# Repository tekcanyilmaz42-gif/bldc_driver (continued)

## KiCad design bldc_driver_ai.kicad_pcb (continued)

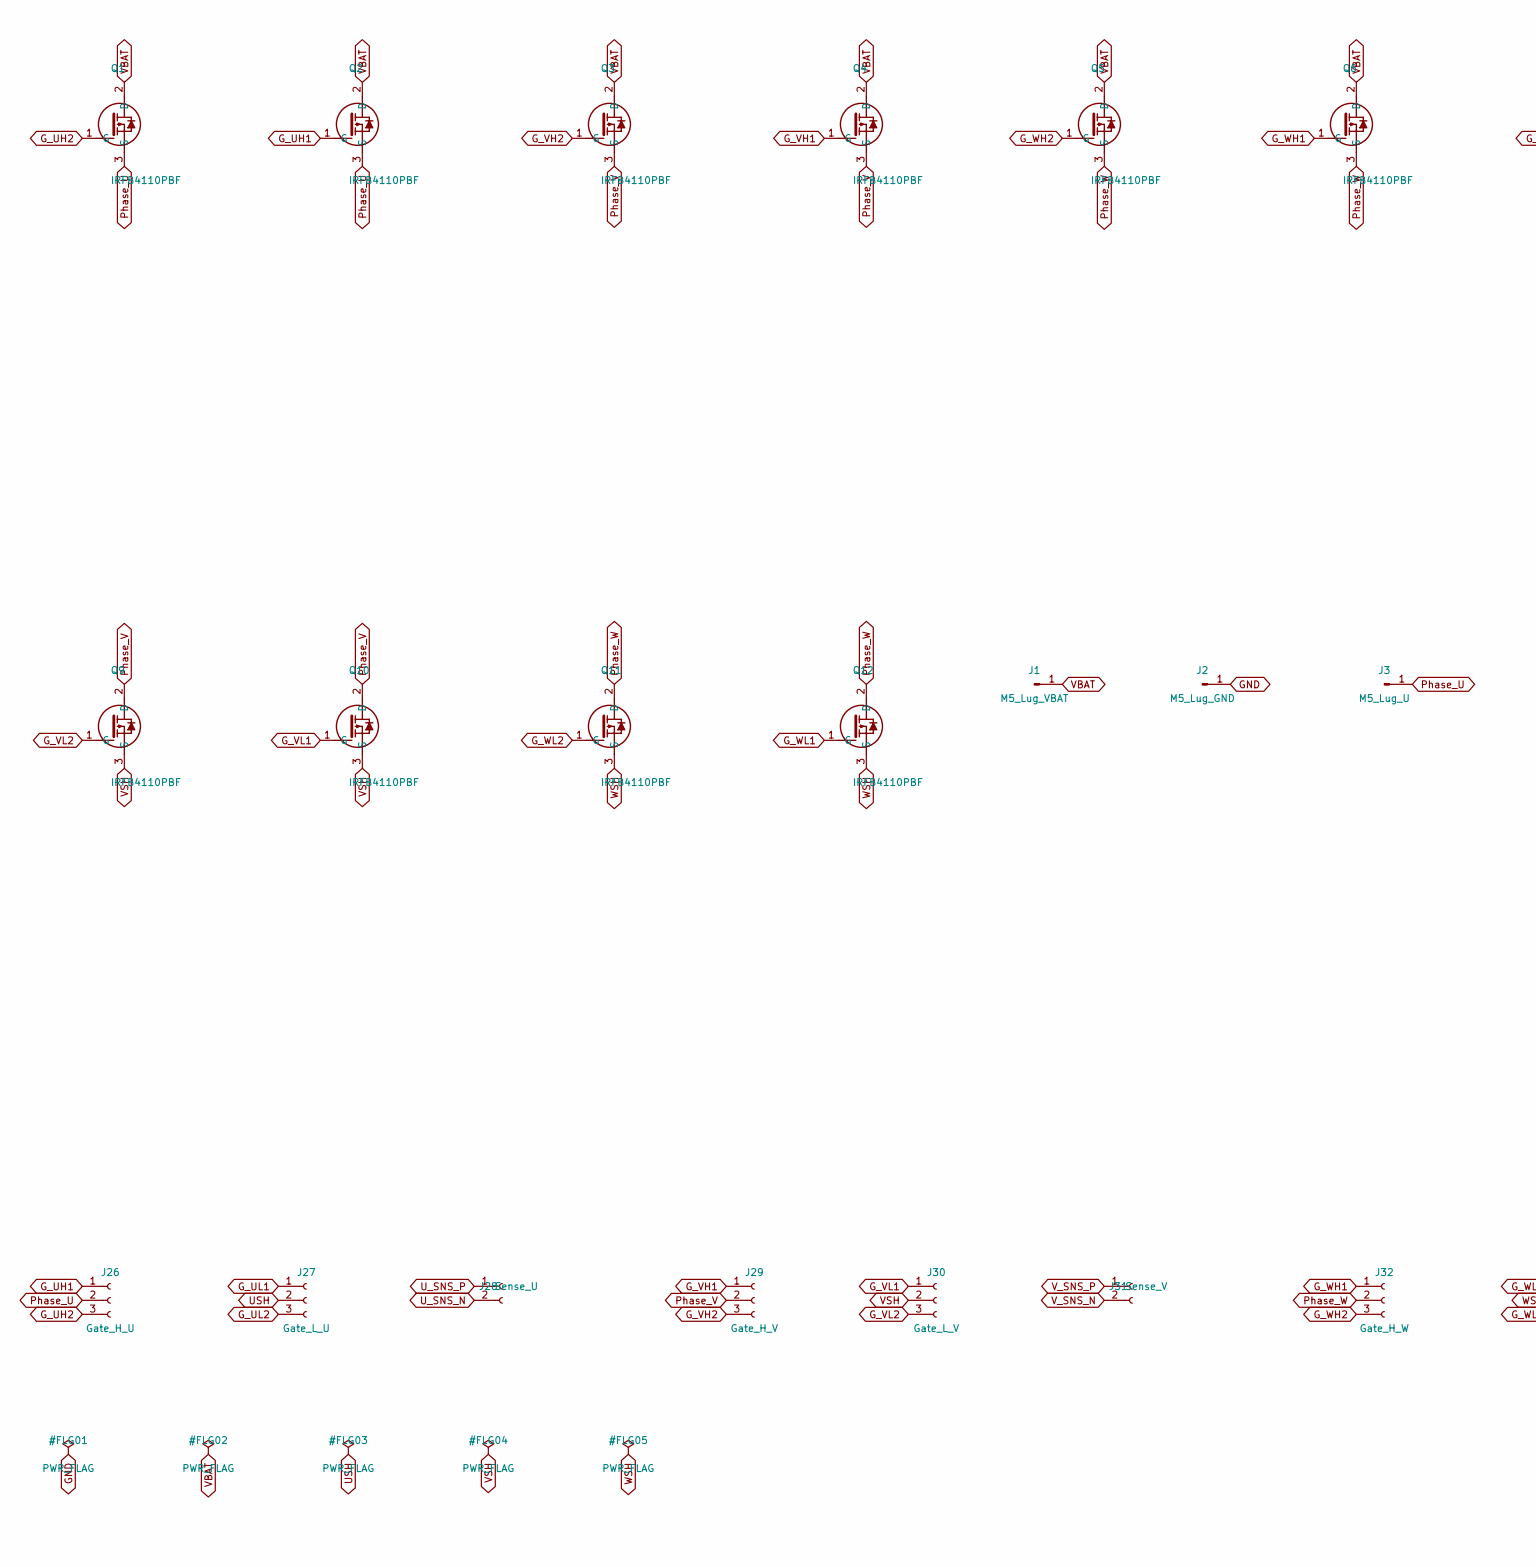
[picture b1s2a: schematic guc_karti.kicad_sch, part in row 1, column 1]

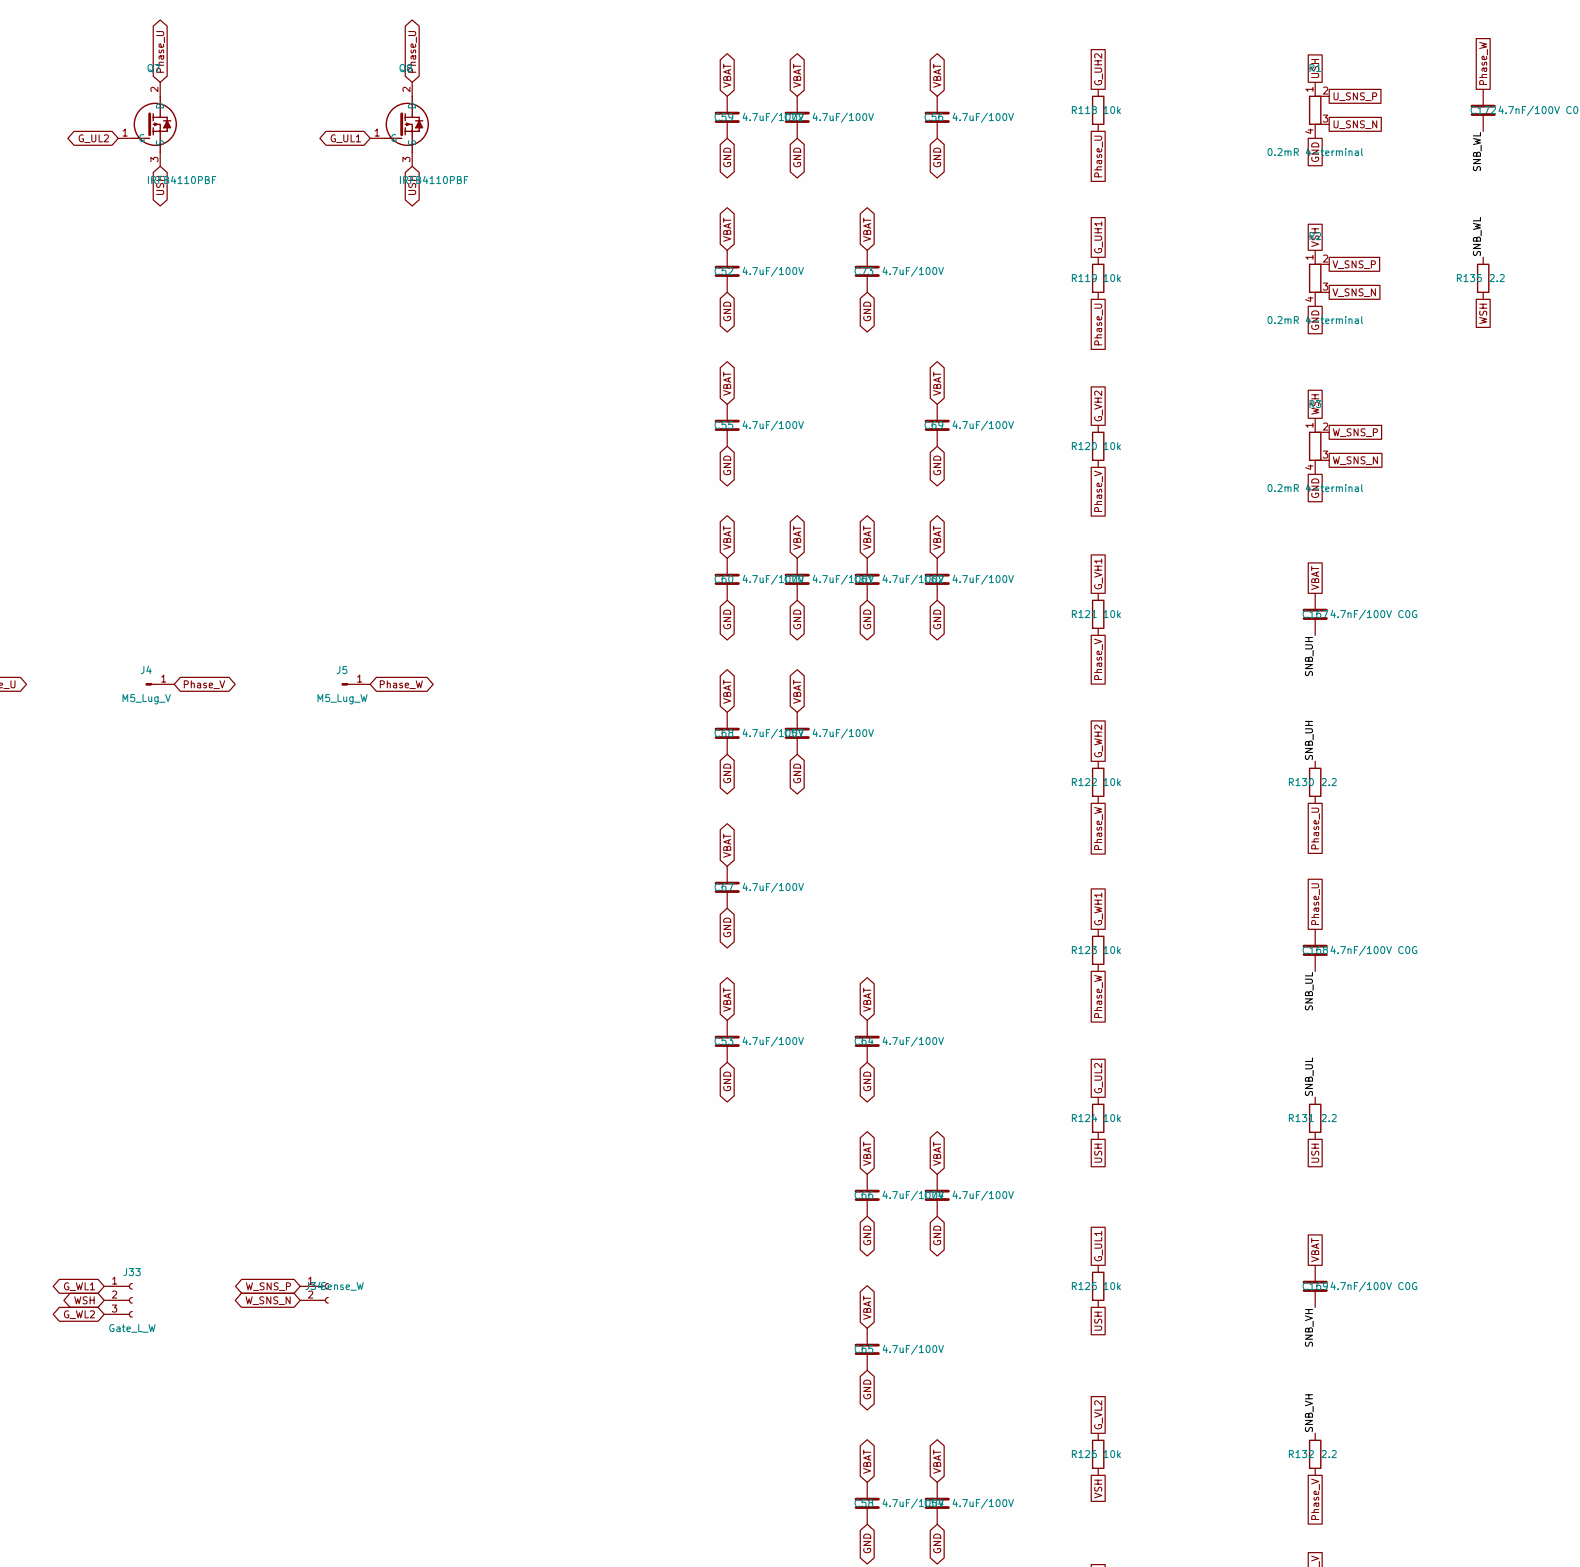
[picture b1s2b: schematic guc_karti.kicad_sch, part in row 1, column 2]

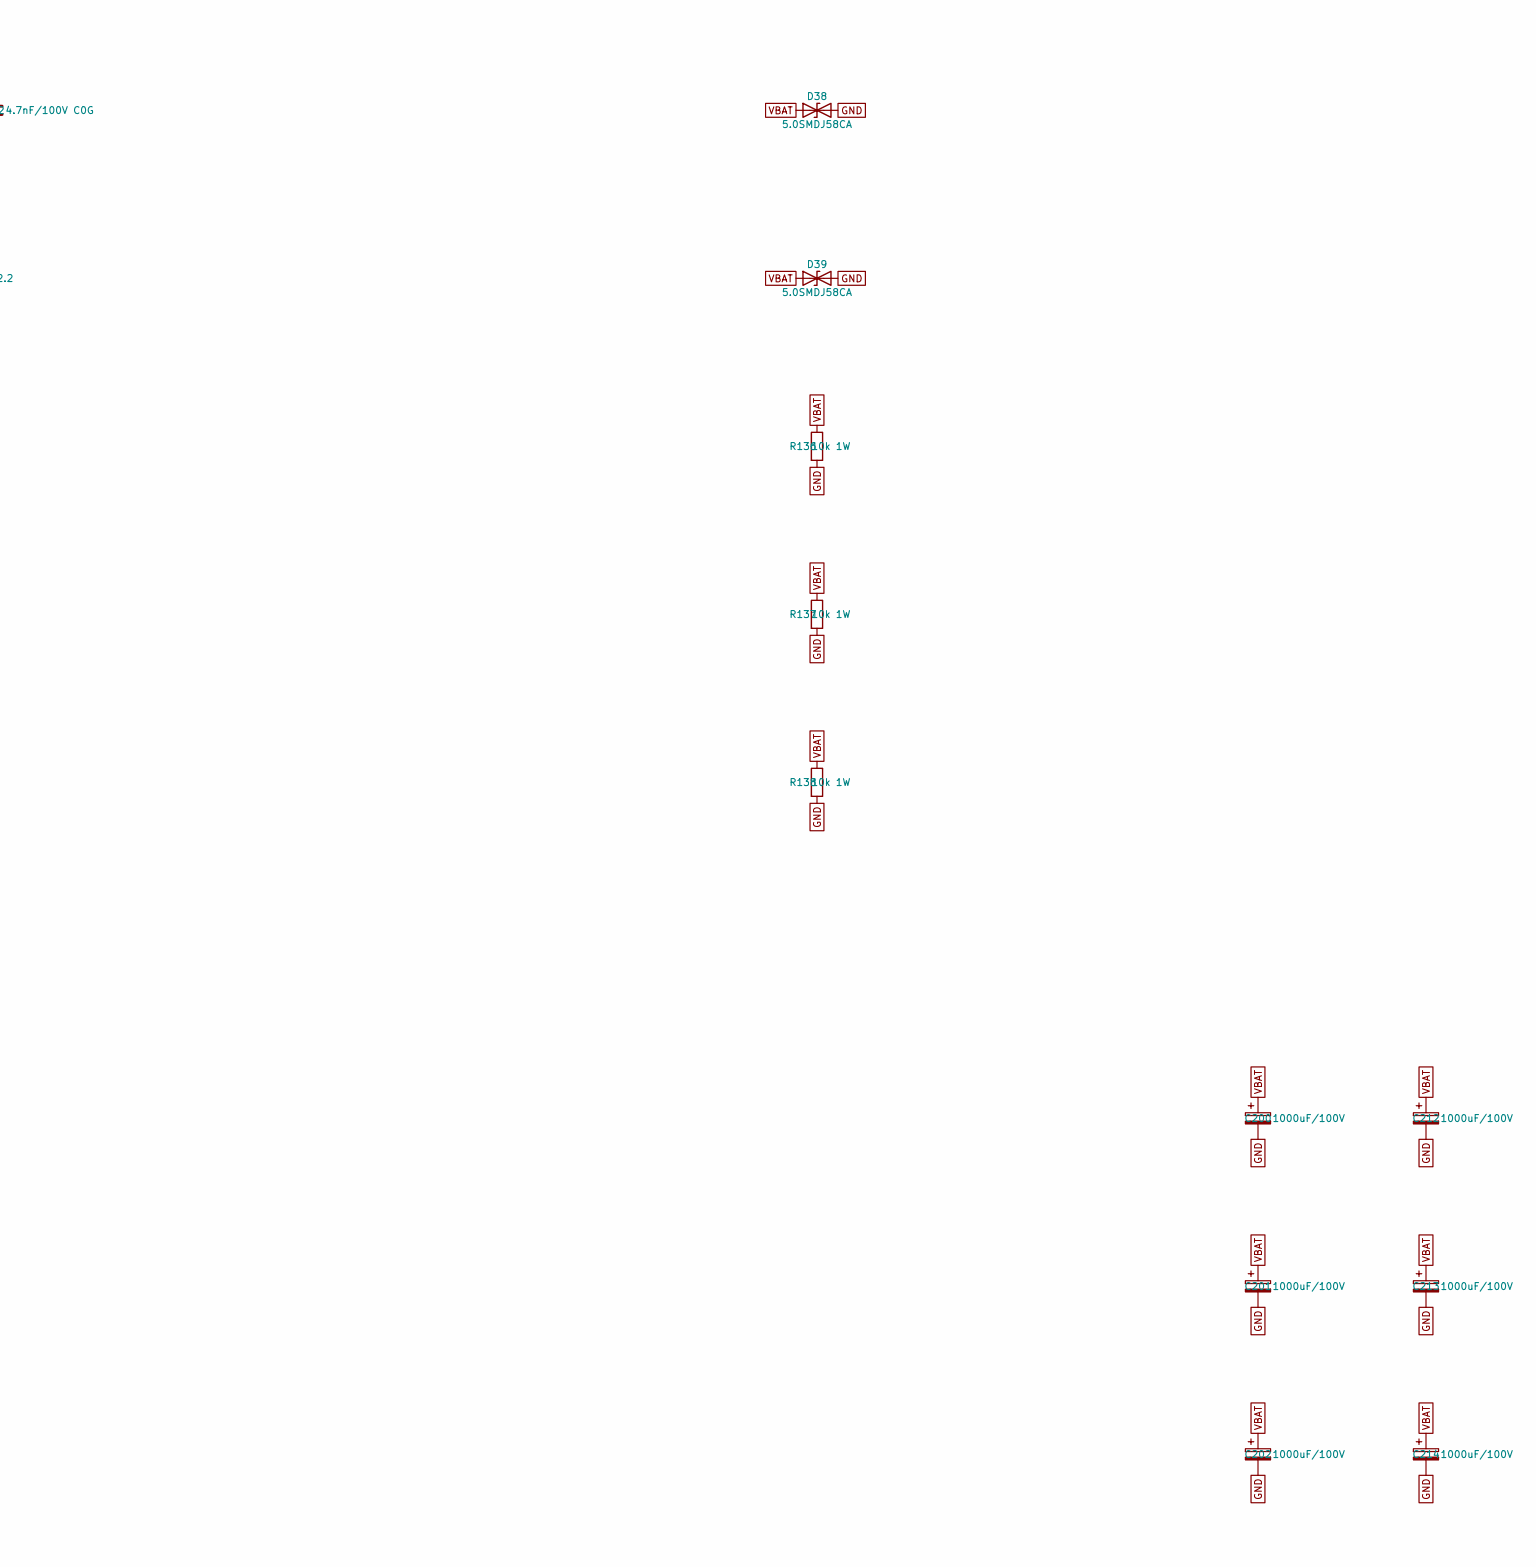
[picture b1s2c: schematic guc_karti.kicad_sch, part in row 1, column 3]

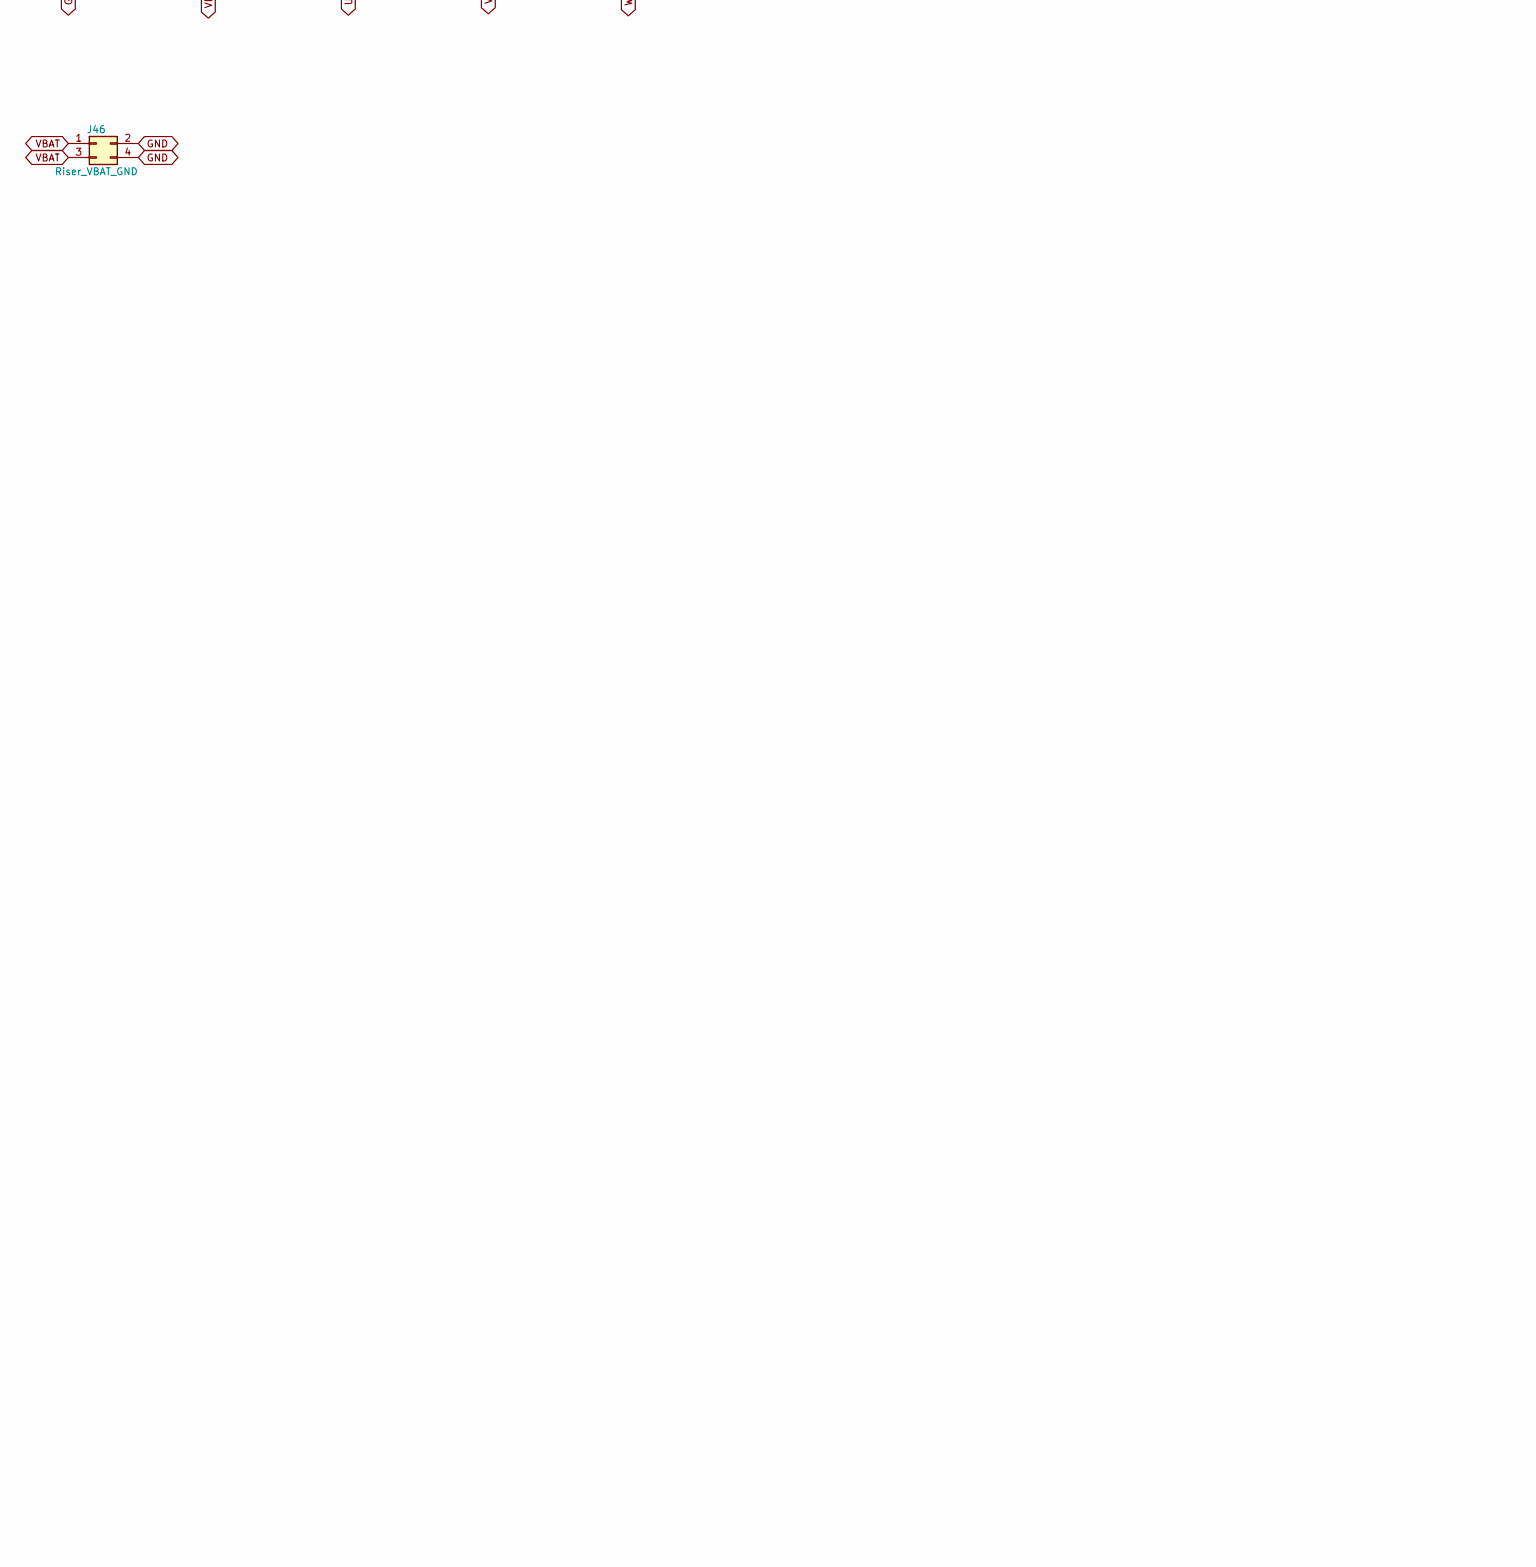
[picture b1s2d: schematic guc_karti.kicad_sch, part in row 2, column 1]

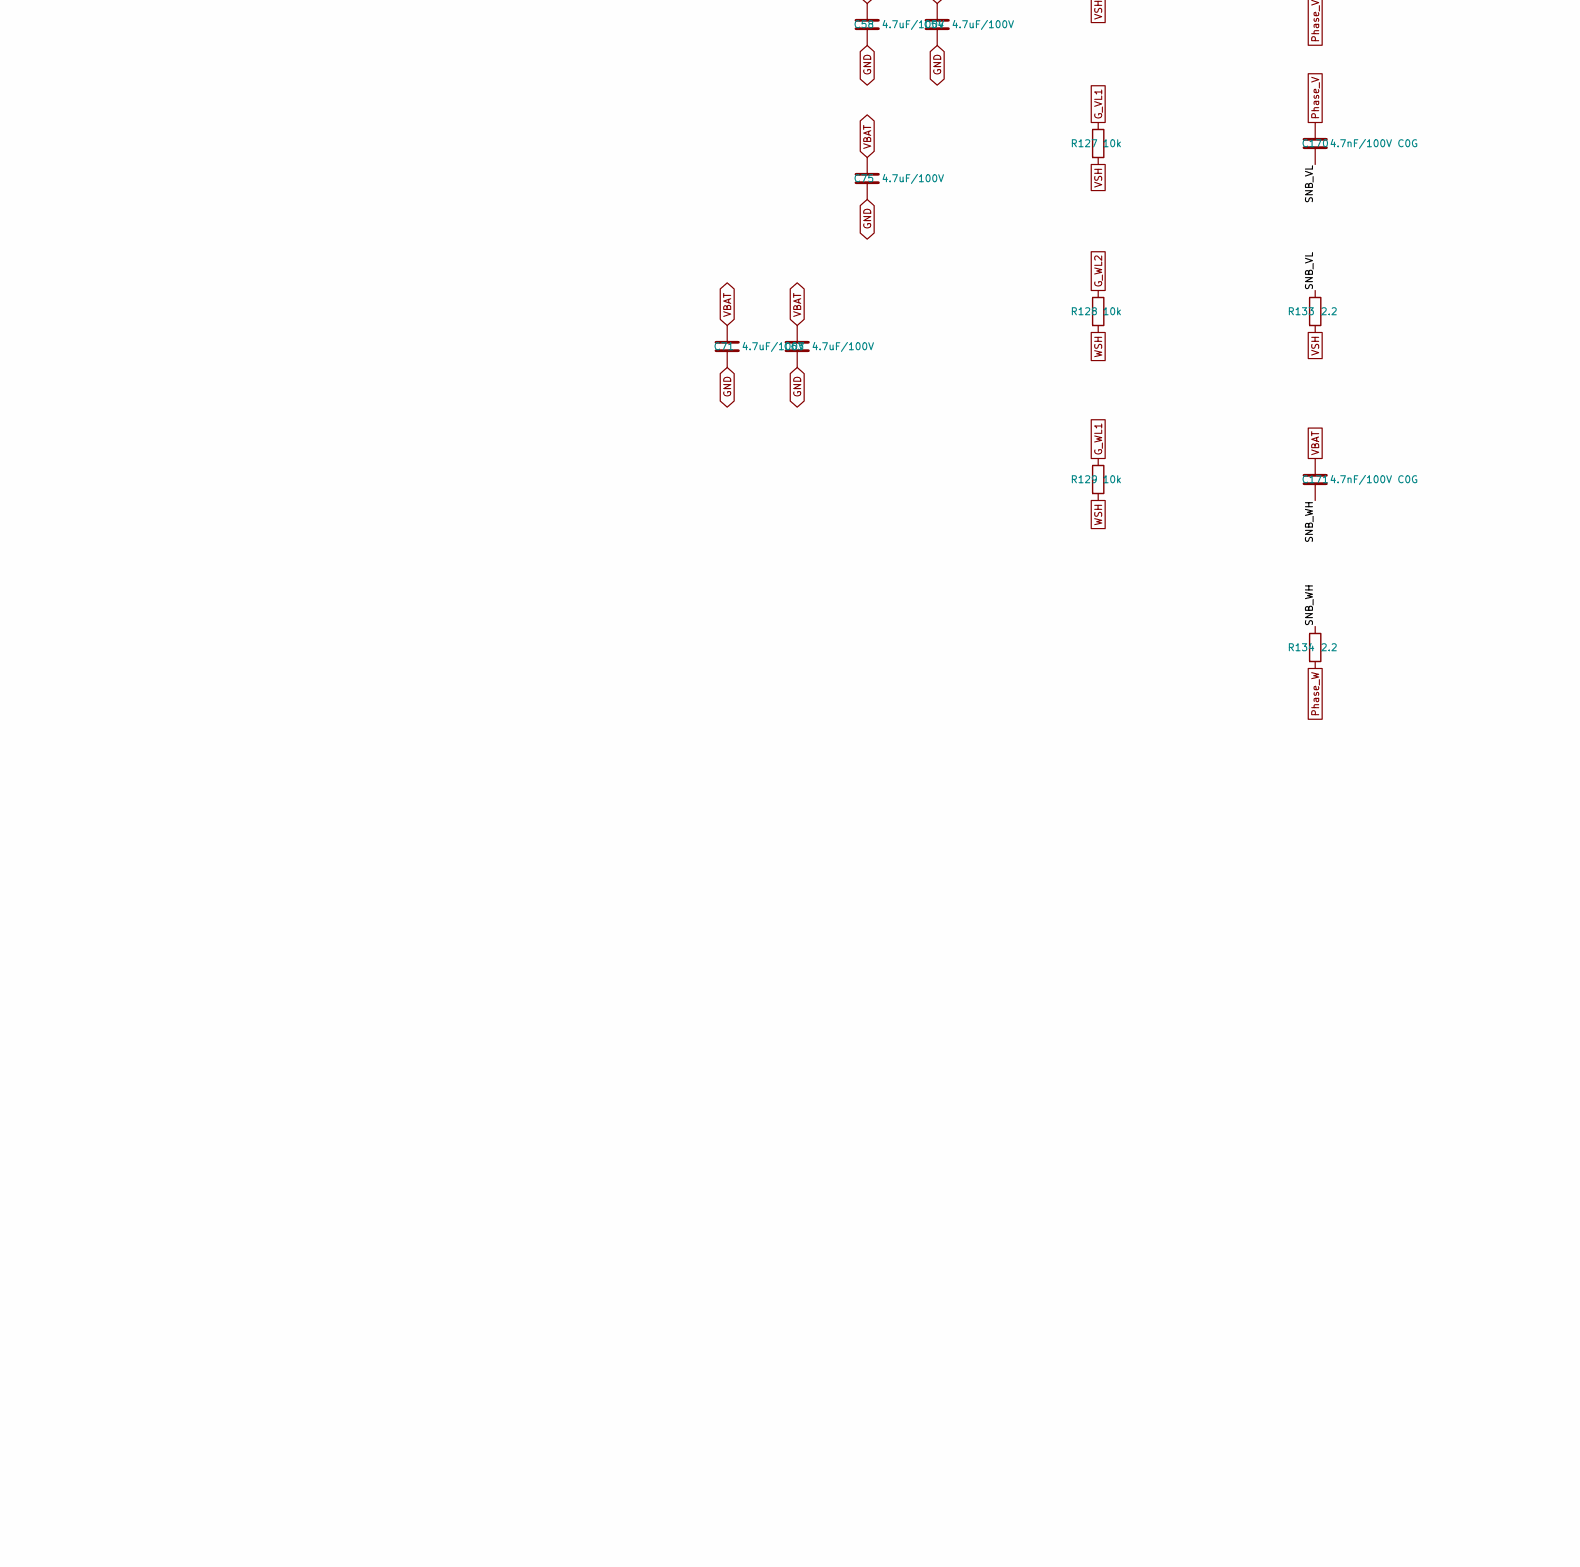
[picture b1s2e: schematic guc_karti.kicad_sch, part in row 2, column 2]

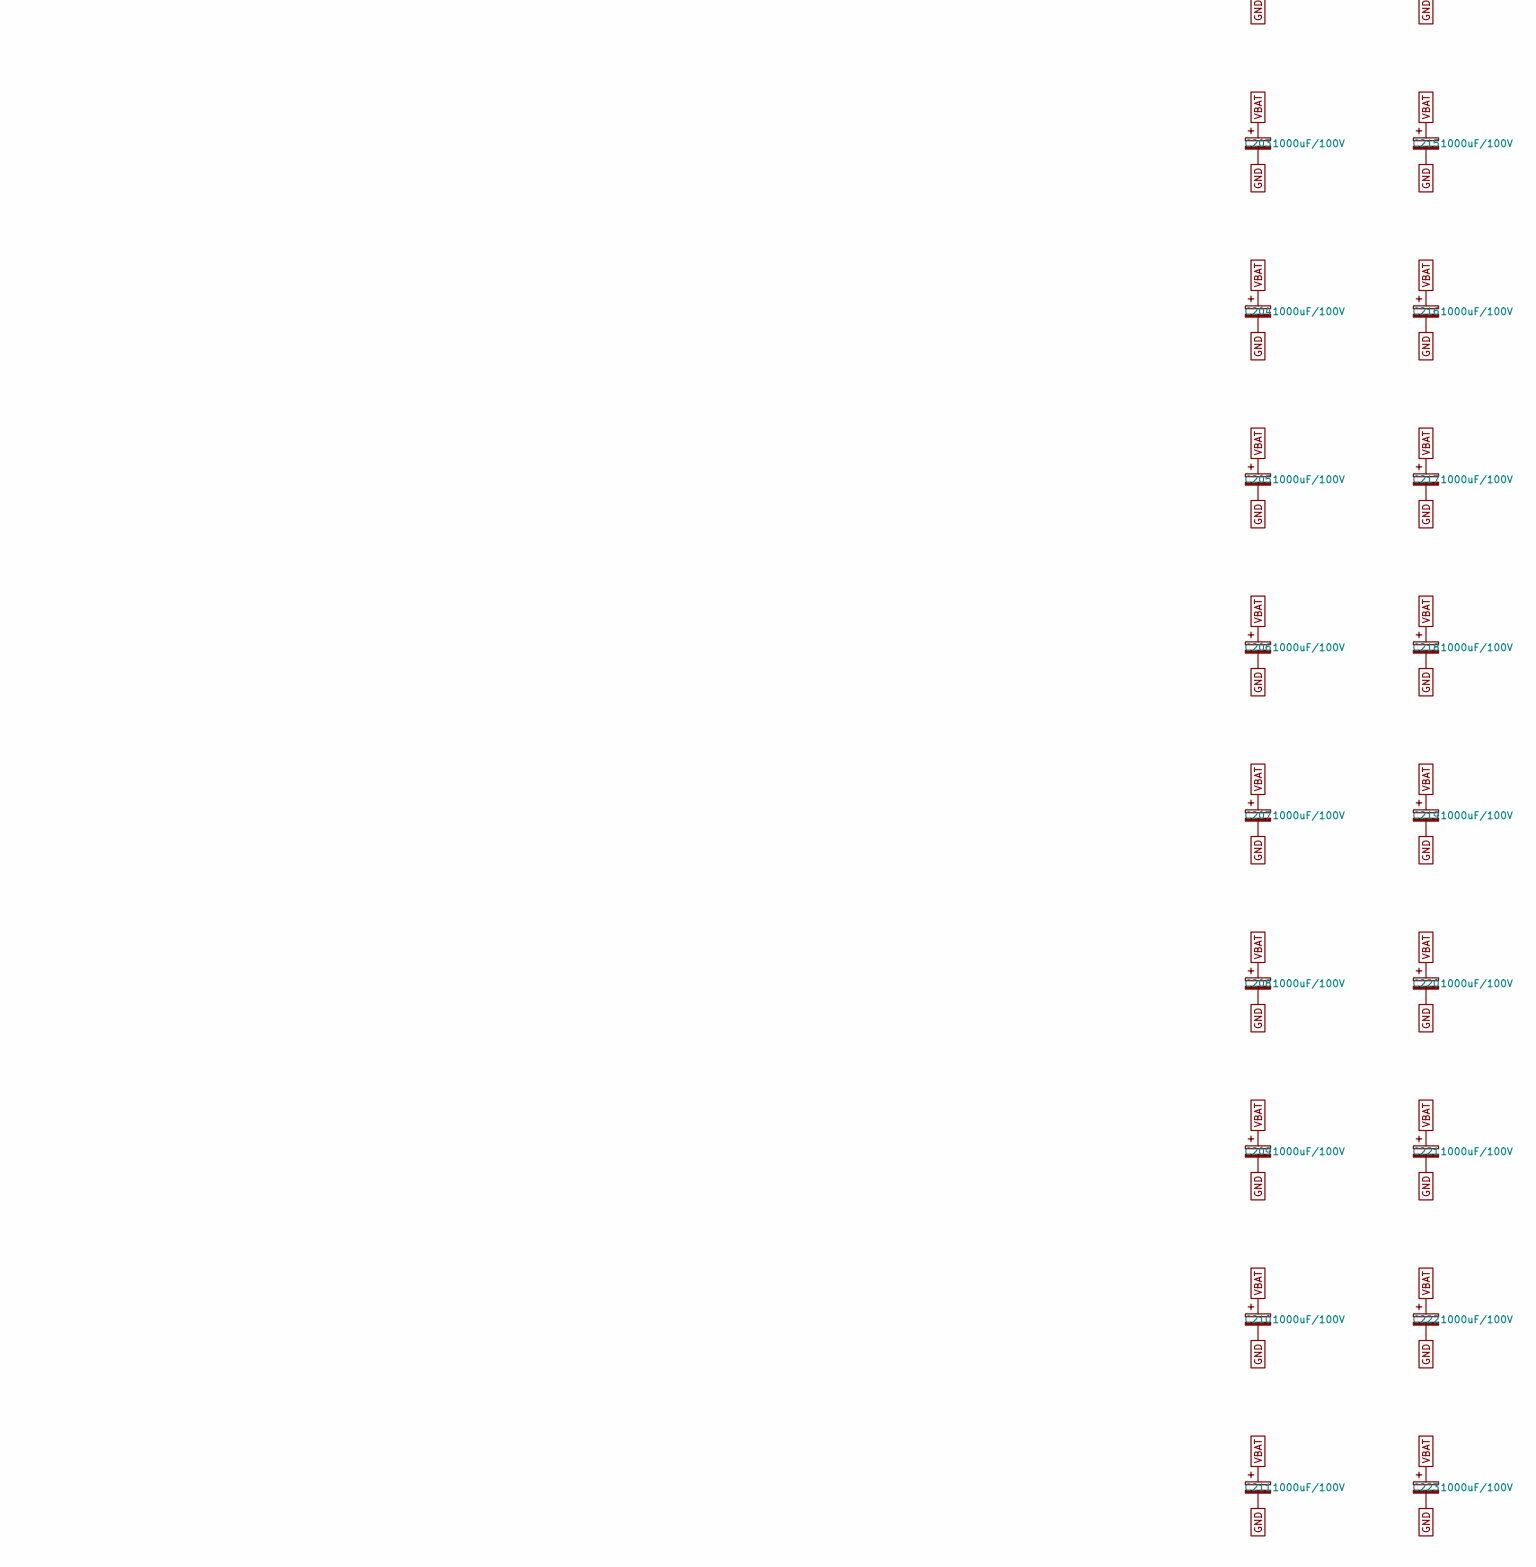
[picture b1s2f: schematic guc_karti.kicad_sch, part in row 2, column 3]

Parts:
C52, C53, C54, C55, C56, C57, C58, C59, C60, C61, C62, C63, C64, C65, C66, C67, C68, C69, C70, C71, C72, C73, C74, C75: 4.7uF/100V; C_1210_3225Metric; MPN GRM32ER72A475KA12L
C167, C168, C169, C170, C171, C172: 4.7nF/100V C0G; C_1206_3216Metric
C200, C201, C202, C203, C204, C205, C206, C207, C208, C209, C210, C211, C212, C213, C214, C215, C216, C217, C218, C219, C220, C221, C222, C223: 1000uF/100V; CP_Radial_D18.0mm_L40mm_P7.50mm_KOSHIN_KLH; MPN PKLH-100V102MK400
D38, D39: 5.0SMDJ58CA; D_SMC; MPN 5.0SMDJ58CA (Littelfuse, 5 kW)
J1: M5_Lug_VBAT; MountingHole_5.3mm_M5_Pad_Via
J2: M5_Lug_GND; MountingHole_5.3mm_M5_Pad_Via
J3: M5_Lug_U; MountingHole_5.3mm_M5_Pad_Via
J4: M5_Lug_V; MountingHole_5.3mm_M5_Pad_Via
J5: M5_Lug_W; MountingHole_5.3mm_M5_Pad_Via
J26: Gate_H_U; PinSocket_1x03_P2.54mm_Vertical
J27: Gate_L_U; PinSocket_1x03_P2.54mm_Vertical
J28: Sense_U; PinSocket_1x02_P2.54mm_Vertical
J29: Gate_H_V; PinSocket_1x03_P2.54mm_Vertical
J30: Gate_L_V; PinSocket_1x03_P2.54mm_Vertical
J31: Sense_V; PinSocket_1x02_P2.54mm_Vertical
J32: Gate_H_W; PinSocket_1x03_P2.54mm_Vertical
J33: Gate_L_W; PinSocket_1x03_P2.54mm_Vertical
J34: Sense_W; PinSocket_1x02_P2.54mm_Vertical
J46: Riser_VBAT_GND; PinSocket_2x02_P2.54mm_Vertical
Q1, Q2, Q3, Q4, Q5, Q6, Q7, Q8, Q9, Q10, Q11, Q12: IRFB4110PBF; TO-220-3_Horizontal_TabUp
R1, R2, R3: 0.2mR 4-terminal; R_Shunt_Isabellenhuette_BVR4026; MPN BVR-Z-R0002-1.0 (Isabellenhuette, 4026,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
R118, R119, R120, R121, R122, R123, R124, R125, R126, R127, R128, R129: 10k; R_0805_2012Metric
R130, R131, R132, R133, R134, R135: 2.2; R_2010_5025Metric
R136, R137, R138: 10k 1W; R_2512_6332Metric

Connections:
/Katman1_Guc_Karti/SNB_UH: C167.2, R130.1
/Katman1_Guc_Karti/SNB_UL: C168.2, R131.1
/Katman1_Guc_Karti/SNB_VH: C169.2, R132.1
/Katman1_Guc_Karti/SNB_VL: C170.2, R133.1
/Katman1_Guc_Karti/SNB_WH: C171.2, R134.1
/Katman1_Guc_Karti/SNB_WL: C172.2, R135.1
GND: C52.2, C53.2, C54.2, C55.2, C56.2, C57.2, C58.2, C59.2, C60.2, C61.2, C62.2, C63.2, C64.2, C65.2, C66.2, C67.2, C68.2, C69.2, C70.2, C71.2, C72.2, C73.2, C74.2, C75.2, C200.2, C201.2, C202.2, C203.2, C204.2, C205.2, C206.2, C207.2, C208.2, C209.2, C210.2, C211.2, C212.2, C213.2, C214.2, C215.2, C216.2, C217.2, C218.2, C219.2, C220.2, C221.2, C222.2, C223.2, D38.2 (A2), D39.2 (A2), J2.1 (Pin_1_1), J46.2, J46.4, R1.4, R2.4, R3.4, R136.2, R137.2, R138.2; also elsewhere on the board
G_UH1: J26.1, Q2.1 (G), R119.1; also elsewhere on the board
G_UH2: J26.3, Q1.1 (G), R118.1; also elsewhere on the board
G_UL1: J27.1, Q8.1 (G), R125.1; also elsewhere on the board
G_UL2: J27.3, Q7.1 (G), R124.1; also elsewhere on the board
G_VH1: J29.1, Q4.1 (G), R121.1; also elsewhere on the board
G_VH2: J29.3, Q3.1 (G), R120.1; also elsewhere on the board
G_VL1: J30.1, Q10.1 (G), R127.1; also elsewhere on the board
G_VL2: J30.3, Q9.1 (G), R126.1; also elsewhere on the board
G_WH1: J32.1, Q6.1 (G), R123.1; also elsewhere on the board
G_WH2: J32.3, Q5.1 (G), R122.1; also elsewhere on the board
G_WL1: J33.1, Q12.1 (G), R129.1; also elsewhere on the board
G_WL2: J33.3, Q11.1 (G), R128.1; also elsewhere on the board
Phase_U: C168.1, J3.1 (Pin_1_1), J26.2, Q1.3 (S), Q2.3 (S), Q7.2 (D), Q8.2 (D), R118.2, R119.2, R130.2; also elsewhere on the board
Phase_V: C170.1, J4.1 (Pin_1_1), J29.2, Q3.3 (S), Q4.3 (S), Q9.2 (D), Q10.2 (D), R120.2, R121.2, R132.2; also elsewhere on the board
Phase_W: C172.1, J5.1 (Pin_1_1), J32.2, Q5.3 (S), Q6.3 (S), Q11.2 (D), Q12.2 (D), R122.2, R123.2, R134.2; also elsewhere on the board
USH: J27.2, Q7.3 (S), Q8.3 (S), R1.1, R124.2, R125.2, R131.2; also elsewhere on the board
U_SNS_N: J28.2, R1.3; also elsewhere on the board
U_SNS_P: J28.1, R1.2; also elsewhere on the board
VBAT: C52.1, C53.1, C54.1, C55.1, C56.1, C57.1, C58.1, C59.1, C60.1, C61.1, C62.1, C63.1, C64.1, C65.1, C66.1, C67.1, C68.1, C69.1, C70.1, C71.1, C72.1, C73.1, C74.1, C75.1, C167.1, C169.1, C171.1, C200.1, C201.1, C202.1, C203.1, C204.1, C205.1, C206.1, C207.1, C208.1, C209.1, C210.1, C211.1, C212.1, C213.1, C214.1, C215.1, C216.1, C217.1, C218.1, C219.1, C220.1, C221.1, C222.1, C223.1, D38.1 (A1), D39.1 (A1), J1.1 (Pin_1_1), J46.1, J46.3, Q1.2 (D), Q2.2 (D), Q3.2 (D), Q4.2 (D), Q5.2 (D), Q6.2 (D), R136.1, R137.1, R138.1; also elsewhere on the board
VSH: J30.2, Q9.3 (S), Q10.3 (S), R2.1, R126.2, R127.2, R133.2; also elsewhere on the board
V_SNS_N: J31.2, R2.3; also elsewhere on the board
V_SNS_P: J31.1, R2.2; also elsewhere on the board
WSH: J33.2, Q11.3 (S), Q12.3 (S), R3.1, R128.2, R129.2, R135.2; also elsewhere on the board
W_SNS_N: J34.2, R3.3; also elsewhere on the board
W_SNS_P: J34.1, R3.2; also elsewhere on the board

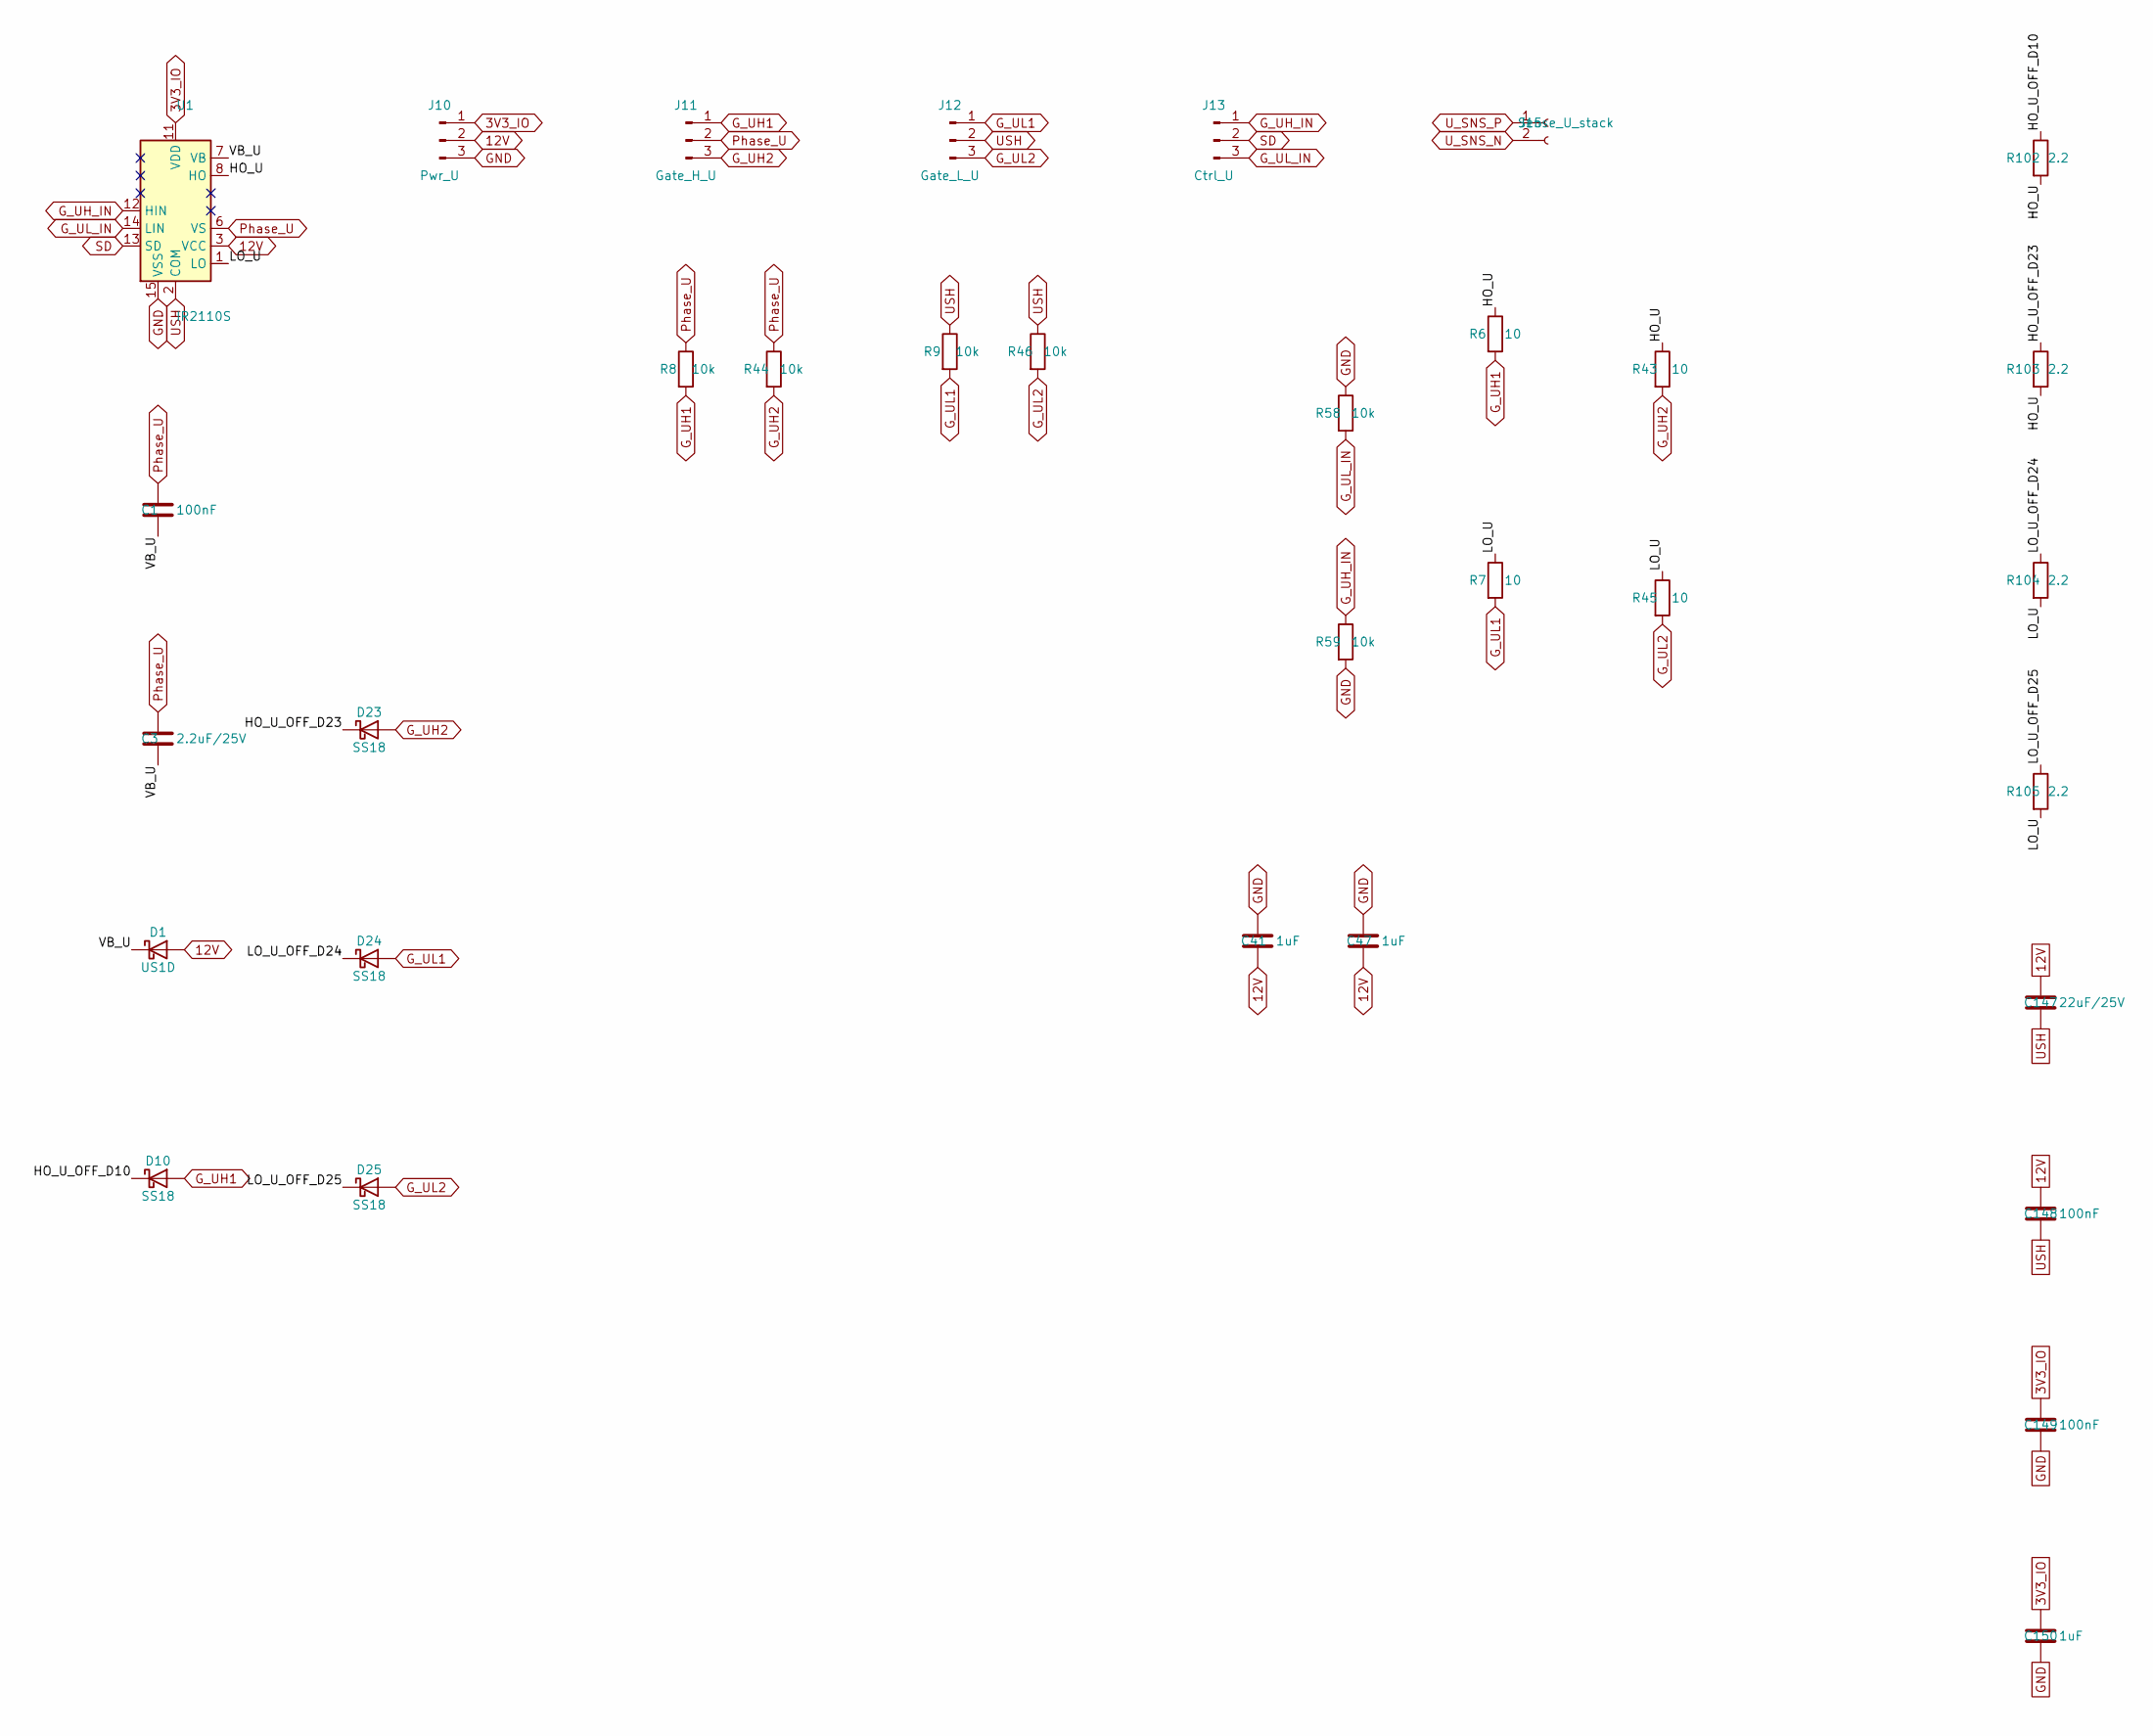
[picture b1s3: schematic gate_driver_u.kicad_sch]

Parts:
C1, C148, C149: 100nF; C_0603_1608Metric
C3: 2.2uF/25V; C_1206_3216Metric; MPN CL31B225KAHNNNE
C41, C47, C150: 1uF; C_0603_1608Metric
C147: 22uF/25V; C_1206_3216Metric; MPN CL31A226KAHNNNE
D1: US1D; D_SMA; MPN US1D-13-F
D10, D23, D24, D25: SS18; D_SMA
J10: Pwr_U; PinHeader_1x03_P2.54mm_Vertical
J11: Gate_H_U; PinHeader_1x03_P2.54mm_Vertical
J12: Gate_L_U; PinHeader_1x03_P2.54mm_Vertical
J13: Ctrl_U; PinHeader_1x03_P2.54mm_Vertical
J15: Sense_U_stack; PinSocket_1x02_P2.54mm_Vertical
R6, R7, R43, R45: 10; R_0805_2012Metric
R8, R9, R44, R46, R58, R59: 10k; R_0603_1608Metric
R102, R103, R104, R105: 2.2; R_0603_1608Metric
U1: IR2110S; SOIC-16W_7.5x10.3mm_P1.27mm

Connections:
3V3_IO: C149.1, C150.1, J10.1, U1.11 (VDD); also elsewhere on the board
12V: C41.2, C47.2, C147.1, C148.1, D1.2 (A), J10.2, U1.3 (VCC); also elsewhere on the board
/Katman2_GateDriver_U/HO_U: R6.1, R43.1, R102.2, R103.2, U1.8 (HO)
/Katman2_GateDriver_U/HO_U_OFF_D10: D10.1 (K), R102.1
/Katman2_GateDriver_U/HO_U_OFF_D23: D23.1 (K), R103.1
/Katman2_GateDriver_U/LO_U: R7.1, R45.1, R104.2, R105.2, U1.1 (LO)
/Katman2_GateDriver_U/LO_U_OFF_D24: D24.1 (K), R104.1
/Katman2_GateDriver_U/LO_U_OFF_D25: D25.1 (K), R105.1
/Katman2_GateDriver_U/VB_U: C1.2, C3.2, D1.1 (K), U1.7 (VB)
GND: C41.1, C47.1, C149.2, C150.2, J10.3, R58.1, R59.2, U1.15 (VSS); also elsewhere on the board
G_UH1: D10.2 (A), J11.1, R6.2, R8.2; also elsewhere on the board
G_UH2: D23.2 (A), J11.3, R43.2, R44.2; also elsewhere on the board
G_UH_IN: J13.1, R59.1, U1.12 (HIN); also elsewhere on the board
G_UL1: D24.2 (A), J12.1, R7.2, R9.2; also elsewhere on the board
G_UL2: D25.2 (A), J12.3, R45.2, R46.2; also elsewhere on the board
G_UL_IN: J13.3, R58.2, U1.14 (LIN); also elsewhere on the board
Phase_U: C1.1, C3.1, J11.2, R8.1, R44.1, U1.6 (VS); also elsewhere on the board
SD: J13.2, U1.13 (SD); also elsewhere on the board
USH: C147.2, C148.2, J12.2, R9.1, R46.1, U1.2 (COM); also elsewhere on the board
U_SNS_N: J15.2; also elsewhere on the board
U_SNS_P: J15.1; also elsewhere on the board
